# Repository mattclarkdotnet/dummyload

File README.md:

# A cheap 2ohm dummy load with 300W power handling

This started as a bit of a joke at audiosciencereview.com, but turned out to work quite well - see thread (https://www.audiosciencereview.com/forum/index.php?threads/silly-surface-mount-dummy-load-module.58077/).

Instead of using large wire wound resistors for dummy loads for amplifier testing, why not use cheap SMD resistors and boards?  This is the result.  a 1.97ohm board.  Yes that's a bit lower than 2ohms in oder to allow for other losses

## Key points

* Single sided aluminium for the board to improve thermal performance
* The heatsinks can be connected to the exposed aluminium on the back of the board, and also to the resistors on the front
* Use 4R7 2W 100ppm 1% resistors 19 parallel and 8 serial, for a total of 1.97ohms per board using 152 resistors. This is to allow a bit of headroom for connector and trace resistance
* Vertical height of 133mm to fit a 140x140mm ducted case
* 2mm wide (1mm internal diameter) thermal vias under each resistor to address the heat buildup from the resistor undersides.
* Using these heatsinks: https://www.aliexpress.com/item/32831608617.html as they are cheap and fit nicely
* M4 holes for cable connection - but note these are only on the top side, you must insulate any screws/bolts/washers on the underside due to the use of single sided aluminium board

## Power handling

These boards are intended to have heatsinks on both sides and be fitted into a 140x140mm ducted case with 140mm fans at each end to evacuate the heat.  Do not run them at high power without high volume forced cooling.  With heatsinks and forced air they can run at 200W/board continuously. 400W per board is easily done with heatsinks and forced air for up to 5 seconds.  Bare boards with no heatsinks or forced air are at your own risk.

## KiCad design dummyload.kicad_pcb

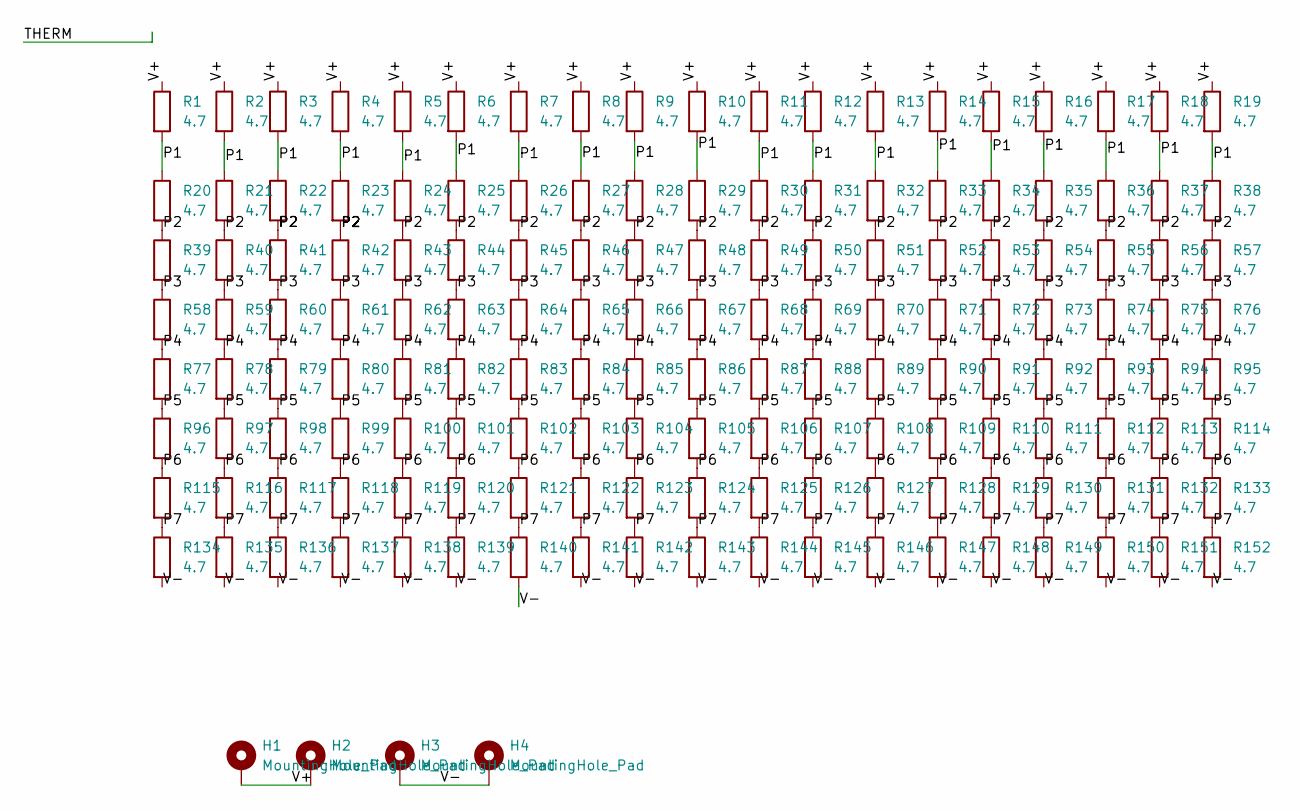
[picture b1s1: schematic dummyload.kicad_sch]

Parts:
H1, H2, H3, H4: MountingHole_Pad; MountingHole_4.3mm_M4_DIN965_Pad_TopOnly
R1, R2, R3, R4, R5, R6, R7, R8, R9, R10, R11, R12, R13, R14, R15, R16, R17, R18, R19, R20, R21, R22, R23, R24, R25, R26, R27, R28, R29, R30, R31, R32, R33, R34, R35, R36, R37, R38, R39, R40, R41, R42, R43, R44, R45, R46, R47, R48, R49, R50, R51, R52, R53, R54, R55, R56, R57, R58, R59, R60, R61, R62, R63, R64, R65, R66, R67, R68, R69, R70, R71, R72, R73, R74, R75, R76, R77, R78, R79, R80, R81, R82, R83, R84, R85, R86, R87, R88, R89, R90, R91, R92, R93, R94, R95, R96, R97, R98, R99, R100, R101, R102, R103, R104, R105, R106, R107, R108, R109, R110, R111, R112, R113, R114, R115, R116, R117, R118, R119, R120, R121, R122, R123, R124, R125, R126, R127, R128, R129, R130, R131, R132, R133, R134, R135, R136, R137, R138, R139, R140, R141, R142, R143, R144, R145, R146, R147, R148, R149, R150, R151, R152: 4.7; R_2512_6332Metric

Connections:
/P1: R1.2, R2.2, R3.2, R4.2, R5.2, R6.2, R7.2, R8.2, R9.2, R10.2, R11.2, R12.2, R13.2, R14.2, R15.2, R16.2, R17.2, R18.2, R19.2, R20.1, R21.1, R22.1, R23.1, R24.1, R25.1, R26.1, R27.1, R28.1, R29.1, R30.1, R31.1, R32.1, R33.1, R34.1, R35.1, R36.1, R37.1, R38.1
/P2: R20.2, R21.2, R22.2, R23.2, R24.2, R25.2, R26.2, R27.2, R28.2, R29.2, R30.2, R31.2, R32.2, R33.2, R34.2, R35.2, R36.2, R37.2, R38.2, R39.1, R40.1, R41.1, R42.1, R43.1, R44.1, R45.1, R46.1, R47.1, R48.1, R49.1, R50.1, R51.1, R52.1, R53.1, R54.1, R55.1, R56.1, R57.1
/P3: R39.2, R40.2, R41.2, R42.2, R43.2, R44.2, R45.2, R46.2, R47.2, R48.2, R49.2, R50.2, R51.2, R52.2, R53.2, R54.2, R55.2, R56.2, R57.2, R58.1, R59.1, R60.1, R61.1, R62.1, R63.1, R64.1, R65.1, R66.1, R67.1, R68.1, R69.1, R70.1, R71.1, R72.1, R73.1, R74.1, R75.1, R76.1
/P4: R58.2, R59.2, R60.2, R61.2, R62.2, R63.2, R64.2, R65.2, R66.2, R67.2, R68.2, R69.2, R70.2, R71.2, R72.2, R73.2, R74.2, R75.2, R76.2, R77.1, R78.1, R79.1, R80.1, R81.1, R82.1, R83.1, R84.1, R85.1, R86.1, R87.1, R88.1, R89.1, R90.1, R91.1, R92.1, R93.1, R94.1, R95.1
/P5: R77.2, R78.2, R79.2, R80.2, R81.2, R82.2, R83.2, R84.2, R85.2, R86.2, R87.2, R88.2, R89.2, R90.2, R91.2, R92.2, R93.2, R94.2, R95.2, R96.1, R97.1, R98.1, R99.1, R100.1, R101.1, R102.1, R103.1, R104.1, R105.1, R106.1, R107.1, R108.1, R109.1, R110.1, R111.1, R112.1, R113.1, R114.1
/P6: R96.2, R97.2, R98.2, R99.2, R100.2, R101.2, R102.2, R103.2, R104.2, R105.2, R106.2, R107.2, R108.2, R109.2, R110.2, R111.2, R112.2, R113.2, R114.2, R115.1, R116.1, R117.1, R118.1, R119.1, R120.1, R121.1, R122.1, R123.1, R124.1, R125.1, R126.1, R127.1, R128.1, R129.1, R130.1, R131.1, R132.1, R133.1
/P7: R115.2, R116.2, R117.2, R118.2, R119.2, R120.2, R121.2, R122.2, R123.2, R124.2, R125.2, R126.2, R127.2, R128.2, R129.2, R130.2, R131.2, R132.2, R133.2, R134.1, R135.1, R136.1, R137.1, R138.1, R139.1, R140.1, R141.1, R142.1, R143.1, R144.1, R145.1, R146.1, R147.1, R148.1, R149.1, R150.1, R151.1, R152.1
/V+: H1.1, H2.1, R1.1, R2.1, R3.1, R4.1, R5.1, R6.1, R7.1, R8.1, R9.1, R10.1, R11.1, R12.1, R13.1, R14.1, R15.1, R16.1, R17.1, R18.1, R19.1
/V-: H3.1, H4.1, R134.2, R135.2, R136.2, R137.2, R138.2, R139.2, R140.2, R141.2, R142.2, R143.2, R144.2, R145.2, R146.2, R147.2, R148.2, R149.2, R150.2, R151.2, R152.2

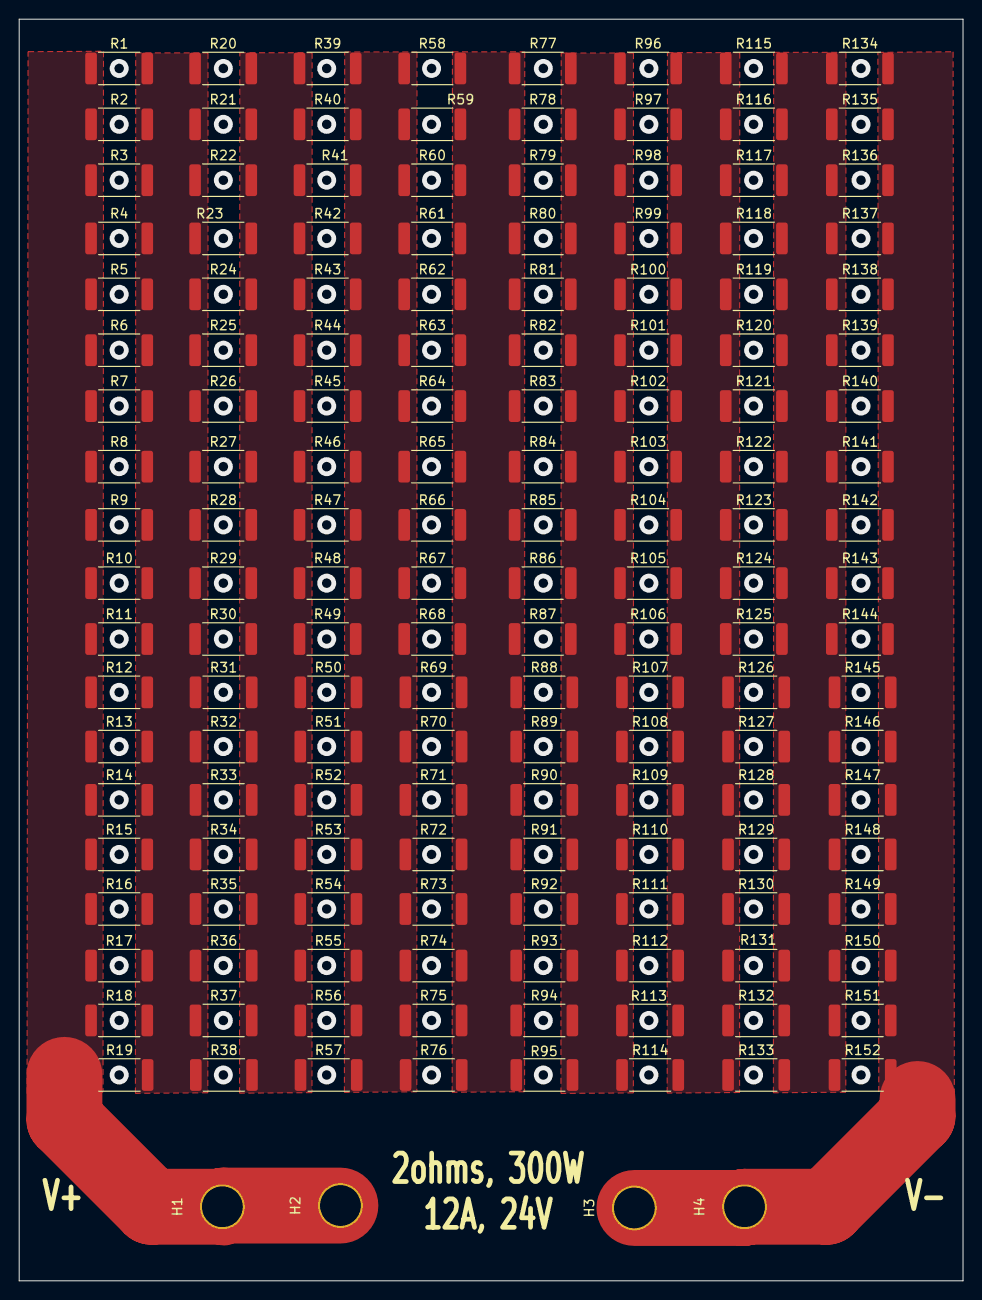
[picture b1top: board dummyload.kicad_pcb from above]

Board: 2 copper layers, 99.5 x 133.0 mm, 156 parts (0 on the bottom side), 9 nets.

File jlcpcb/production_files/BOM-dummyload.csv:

Comment,Designator,Footprint,LCSC
4.7,"R1,R10,R100,R101,R102,R103,R104,R105,R106,R107,R108,R109,R11,R110,R111,R112,R113,R114,R115,R116,R117,R118,R119,R12,R120,R121,R122,R123,R124,R125,R126,R127,R128,R129,R13,R130,R131,R132,R133,R134,R135,R136,R137,R138,R139,R14,R140,R141,R142,R143,R144,R145,R146,R147,R148,R149,R15,R150,R151,R152,R16,R17,R18,R19,R2,R20,R21,R22,R23,R24,R25,R26,R27,R28,R29,R3,R30,R31,R32,R33,R34,R35,R36,R37,R38,R39,R4,R40,R41,R42,R43,R44,R45,R46,R47,R48,R49,R5,R50,R51,R52,R53,R54,R55,R56,R57,R58,R59,R6,R60,R61,R62,R63,R64,R65,R66,R67,R68,R69,R7,R70,R71,R72,R73,R74,R75,R76,R77,R78,R79,R8,R80,R81,R82,R83,R84,R85,R86,R87,R88,R89,R9,R90,R91,R92,R93,R94,R95,R96,R97,R98,R99",R_2512_6332Metric,C305271

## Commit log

2024-12-18 Added core KiCAD files
2024-12-18 Added gerbers
2024-12-19 fixed (removed) thermal reliefs on the one zone that was missing them
2024-12-19 made V+ and V- races thicker (8mm instead of 5). This required movig the resistor banks slightly closer together. Overall should reduce resistance of traces and zones without thermal impact
2024-12-19 updated production files
2026-01-31 whatever that change was, prepping to make v2
